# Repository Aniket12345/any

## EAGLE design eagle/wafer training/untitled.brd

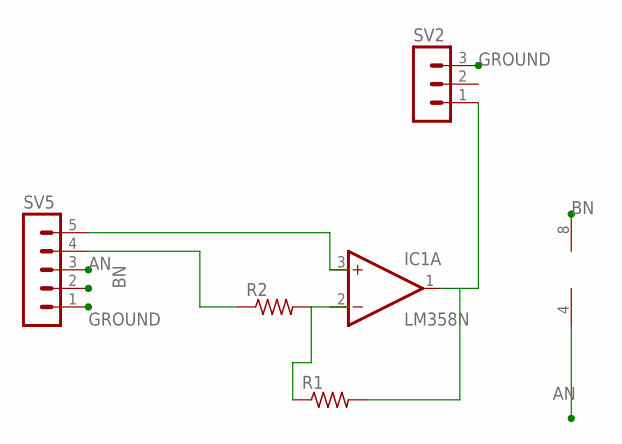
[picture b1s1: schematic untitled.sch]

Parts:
IC1: LM358N; DIL08
R1, R2: R-US_0204/2V; 0204V
SV2: MA03-1
SV5: MA05-1

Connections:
AN: IC1.4 (V-), SV5.3
BN: IC1.8 (V+), SV5.2
GROUND: SV2.3, SV5.1
unnamed: R1.1, R2.2
unnamed: IC1.1 (OUT), R1.2, SV2.1
unnamed: IC1.3 (+IN), SV5.5
unnamed: R2.1, SV5.4

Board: 2 copper layers, 5 parts (0 on the bottom side), 7 nets, no tracks yet.

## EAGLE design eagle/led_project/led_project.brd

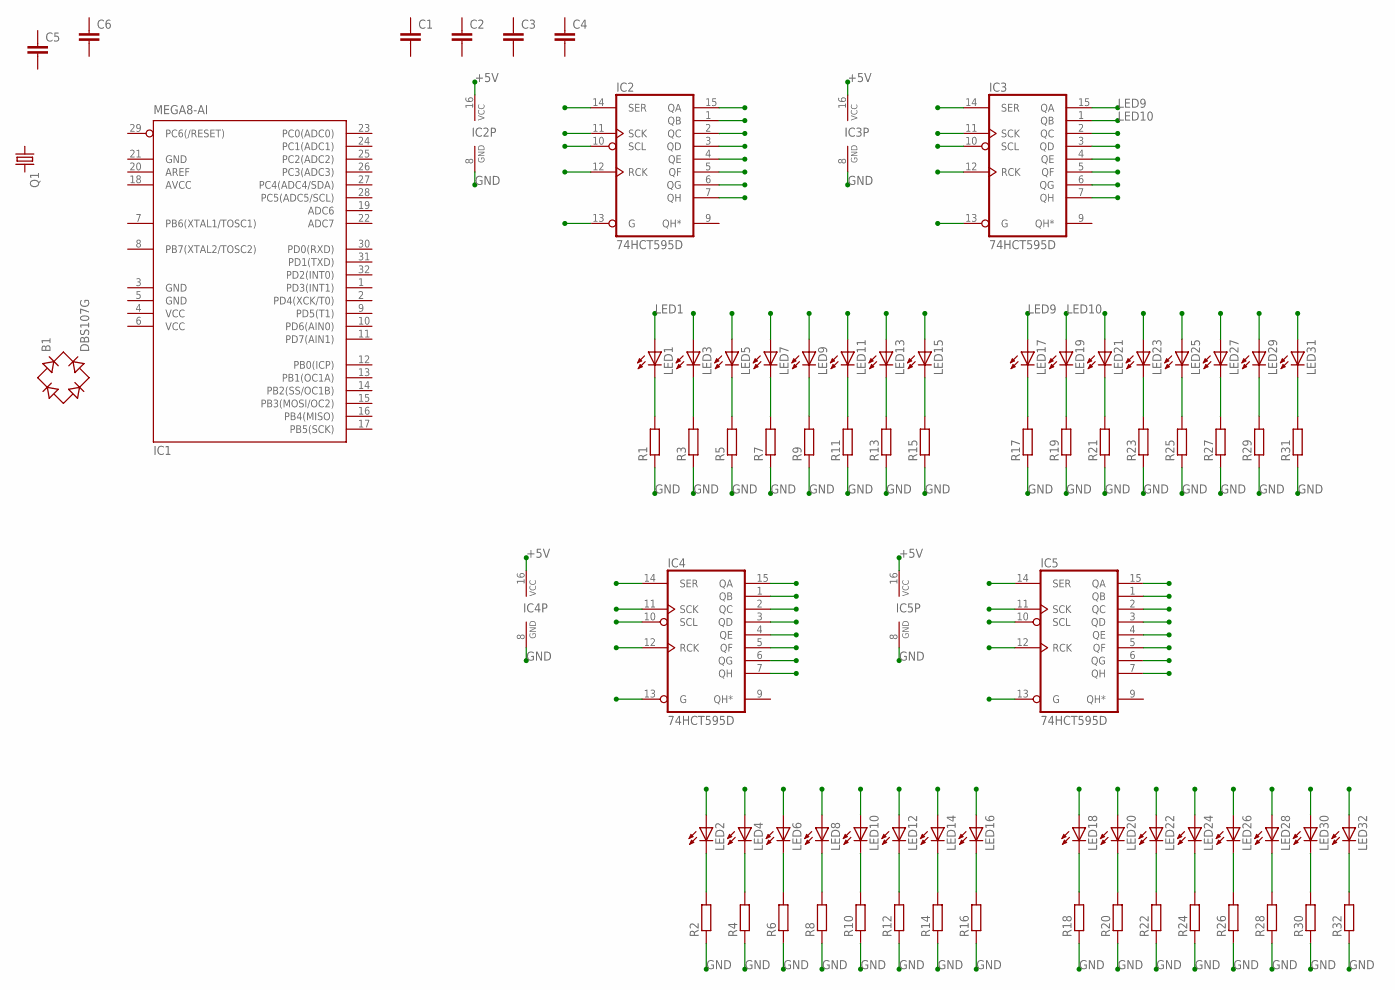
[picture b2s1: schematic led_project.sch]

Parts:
B1: DBS107G; DBS
C1, C2, C3, C4, C5, C6: C-EUC1206K; C1206K
IC1: MEGA8-AI; TQFP32-08
IC2, IC3, IC4, IC5: 74HCT595D; SO16
LED1, LED2, LED3, LED4, LED5, LED6, LED7, LED8, LED9, LED10, LED11, LED12, LED13, LED14, LED15, LED16, LED17, LED18, LED19, LED20, LED21, LED22, LED23, LED24, LED25, LED26, LED27, LED28, LED29, LED30, LED31, LED32: LEDCHIPLED_1206; CHIPLED_1206
Q1: CRYSTALHC49UP; HC49UP
R1, R2, R3, R4, R5, R6, R7, R8, R9, R10, R11, R12, R13, R14, R15, R16, R17, R18, R19, R20, R21, R22, R23, R24, R25, R26, R27, R28, R29, R30, R31, R32: R-EU_R1206; R1206

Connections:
+5V: IC2.16 (VCC), IC3.16 (VCC), IC4.16 (VCC), IC5.16 (VCC)
AVCC: IC1.18 (AVCC)
GND: IC1.3 (GND), IC1.5 (GND), IC1.21 (GND), IC2.8 (GND), IC3.8 (GND), IC4.8 (GND), IC5.8 (GND), R1.1, R2.1, R3.1, R4.1, R5.1, R6.1, R7.1, R8.1, R9.1, R10.1, R11.1, R12.1, R13.1, R14.1, R15.1, R16.1, R17.1, R18.1, R19.1, R20.1, R21.1, R22.1, R23.1, R24.1, R25.1, R26.1, R27.1, R28.1, R29.1, R30.1, R31.1, R32.1
LED1: IC2.15 (QA), LED1.A
LED2: IC2.1 (QB), LED3.A
LED3: IC2.2 (QC), LED5.A
LED4: IC2.3 (QD), LED7.A
LED5: IC2.4 (QE), LED9.A
LED6: IC2.5 (QF), LED11.A
LED7: IC2.6 (QG), LED13.A
LED8: IC2.7 (QH), LED15.A
LED9: IC3.15 (QA), LED17.A
LED10: IC3.1 (QB), LED19.A
LED11: IC3.2 (QC), LED21.A
LED12: IC3.3 (QD), LED23.A
LED13: IC3.4 (QE), LED25.A
LED14: IC3.5 (QF), LED27.A
LED15: IC3.6 (QG), LED29.A
LED16: IC3.7 (QH), LED31.A
LED17: IC4.15 (QA), LED2.A
LED18: IC4.1 (QB), LED4.A
LED19: IC4.2 (QC), LED6.A
LED20: IC4.3 (QD), LED8.A
LED21: IC4.4 (QE), LED10.A
LED22: IC4.5 (QF), LED12.A
LED23: IC4.6 (QG), LED14.A
LED24: IC4.7 (QH), LED16.A
LED25: IC5.15 (QA), LED18.A
LED26: IC5.1 (QB), LED20.A
LED27: IC5.2 (QC), LED22.A
LED28: IC5.3 (QD), LED24.A
LED29: IC5.4 (QE), LED26.A
LED30: IC5.5 (QF), LED28.A
LED31: IC5.6 (QG), LED30.A
LED32: IC5.7 (QH), LED32.A
unnamed: LED1.C, R1.2
unnamed: LED3.C, R3.2
unnamed: LED5.C, R5.2
unnamed: LED7.C, R7.2
unnamed: LED9.C, R9.2
unnamed: LED11.C, R11.2
unnamed: LED13.C, R13.2
unnamed: LED15.C, R15.2
unnamed: LED17.C, R17.2
unnamed: LED19.C, R19.2
unnamed: LED21.C, R21.2
unnamed: LED23.C, R23.2
unnamed: LED25.C, R25.2
unnamed: LED27.C, R27.2
unnamed: LED29.C, R29.2
unnamed: LED31.C, R31.2
unnamed: LED2.C, R2.2
unnamed: LED4.C, R4.2
unnamed: LED6.C, R6.2
unnamed: LED8.C, R8.2
unnamed: LED10.C, R10.2
unnamed: LED12.C, R12.2
unnamed: LED14.C, R14.2
unnamed: LED16.C, R16.2
unnamed: LED18.C, R18.2
unnamed: LED20.C, R20.2
unnamed: LED22.C, R22.2
unnamed: LED24.C, R24.2
unnamed: LED26.C, R26.2
unnamed: LED28.C, R28.2
unnamed: LED30.C, R30.2
unnamed: LED32.C, R32.2
VCC: IC1.4 (VCC), IC1.6 (VCC)

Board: 2 copper layers, 77 parts (2 on the bottom side), 67 nets, no tracks yet.

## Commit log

2017-04-15 hellow git
2017-04-15 hellow aniket
2017-04-15 hellow wafer
2017-04-15 5 more line
2017-04-15 5 more line change
